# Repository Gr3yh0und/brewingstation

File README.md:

# Brewing Station

Firmware, hardware, and PCB design for a DIY automated beer brewing controller. An ESP32-based device reads mash temperature from multiple sensors, drives a [GGM IDS2 induction cooktop](https://www.ggmgastro.com/de-de-eur/induktionsherd-3-5-kw-1) through PID control, and integrates with [CraftBeerPi](https://web.craftbeerpi.com/) via MQTT.

This repo tracks the project's evolution across several hardware/firmware generations.

Credit: the GGM IDS2 induction cooktop's RS232/serial protocol — pulse timings, command frames, power levels, and error codes — was reverse-engineered by [InnuendoPi](https://github.com/InnuendoPi) in [MQTTDevice2](https://github.com/InnuendoPi/MQTTDevice2). Every generation in this repo builds on that work.

## Own projects (in order of development)

| Folder | Status | Board | Build system | Notes |
|---|---|---|---|---|
| [brewingstation](brewingstation/) | V1 | ESP32 (DOIT ESP32 DEVKIT V1) | Arduino IDE (`.ino`) or PlatformIO | One firmware, two hardware variants: [breadboard](brewingstation/hardware/breadboard/) and [fabricated PCB](brewingstation/hardware/pcb/). Documented in its own [README](brewingstation/README.md). |
| [brewingstation3](brewingstation3/) | **WIP** | ESP32-C6-WROOM-1U | PlatformIO | Full rewrite: PID mash control, multi-sensor support, safety shutdowns, brew timer, KiCad schematic, 3D-printable case. See [README](brewingstation3/README.md), [HARDWARE.md](brewingstation3/HARDWARE.md), [BOM.md](brewingstation3/BOM.md), [CASE.md](brewingstation3/CASE.md). |

`brewingstation` carries a `platformio.ini` (`src_dir = .`) alongside its `.ino`, so both PlatformIO and the Arduino IDE build from the same source file — pick whichever toolchain you prefer.

All generations share the same core idea: control the GGM IDS2 induction cooktop over its proprietary serial protocol, read temperature from DS18B20/PT100/PT1000/BME sensors, drive a couple of OLED displays and status LEDs, and talk to CraftBeerPi over MQTT.

`brewingstation3` is where active development happens; the earlier folders are kept as historical/reference hardware revisions. It is **work in progress**: firmware compiles but is not yet proven on real hardware — the PCB hasn't been soldered/assembled, nothing has been tested end-to-end, and the 3D-printable case hasn't been printed.

## Getting started

Each own-project folder is self-contained with its own README and config. In general:

1. Pick a generation — `brewingstation3` for new builds, the earlier folders for reference or repairing existing hardware.
2. Copy `config_example.h` (or `include/config_example.h` for `brewingstation3`) to `config.h` and fill in your MQTT/OTA settings (`brewingstation3` also provisions WiFi separately, via a WiFiManager captive portal on first boot — see its README). `config.h` is gitignored — never commit real credentials.
3. Build with PlatformIO (`pio run`) or open the `.ino` directly in the Arduino IDE — see that folder's README for board-specific notes.

The whole repo can also be opened as a single VS Code workspace via [brewingstation.code-workspace](brewingstation.code-workspace).

## Testing

`brewingstation3` has a native unit test suite for its hardware-independent logic (calibration math, button-ladder mapping, induction error codes) — runs on the host, no ESP32 toolchain or device required:

```sh
cd brewingstation3
pio test -e native
```

CI runs both the firmware build and this test suite on every push — see the badge above or [.github/workflows/build-brewingstation3.yml](.github/workflows/build-brewingstation3.yml).

## License

[MIT](LICENSE) — see [LICENSE](LICENSE) for the full text.

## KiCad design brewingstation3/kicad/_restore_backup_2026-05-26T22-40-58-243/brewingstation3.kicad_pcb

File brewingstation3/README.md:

# Brewing Station 3

Automated beer brewing temperature controller. Reads temperature from multiple sensors, controls a GGM IDS2 induction cooker via a proprietary serial protocol, and runs a PID loop to hold a target mash temperature. Integrates with CraftBeerPi 3 and 4 via MQTT.

**Status: work in progress.** Firmware compiles but is not yet proven on real hardware — the PCB hasn't been soldered/assembled, nothing has been tested end-to-end, and the 3D-printable case hasn't been printed.

**Board:** ESP32-C6-WROOM-1U (ESP32-C6-DevKitC-1-N8)  
**Toolchain:** PlatformIO + VS Code (see [platformio.ini](platformio.ini))  
**Schematic:** KiCad 10 — see [kicad/](kicad/)

| Document | Contents |
|---|---|
| [HARDWARE.md](HARDWARE.md) | Sensors, actuators, connectors, pin map, IDS2 protocol, displays |
| [BOM.md](BOM.md) | Full bill of materials with order links |
| [CASE.md](CASE.md) | 3D-printable enclosure — dimensions, assembly, panel layout |

## Releases

Versioned as `3.0.0-alpha.N` (SemVer, pre-1.0 track) while the hardware is unverified — every [release](../../releases) is marked **pre-release** on GitHub until the PCB is built, soldered, and confirmed working end-to-end, at which point it graduates to `3.0.0`. Tags use a plain `3.*` pattern (no `v` prefix) to avoid colliding with `brewingstation` (V1)'s `vX.Y.Z` tags.

Cutting a release: `git tag 3.0.0-alpha.N && git push origin 3.0.0-alpha.N` — this runs the native test suite as a gate, then builds and publishes binaries, a KiCad design snapshot, and the case source to a GitHub Release. See [.github/workflows/release-brewingstation3.yml](../.github/workflows/release-brewingstation3.yml).

---

## Software Features

### Brewing Control
- **PID temperature control** — Proportional on Measurement (P_ON_M) mode. Default tuning: P=45.27, I=0.2371, D=7.2. All parameters adjustable at runtime via MQTT. Setpoint can be configured while PID is off.
- **Induction cooker control** — GGM IDS2 controlled via a proprietary 33-bit pulse-width serial protocol. 6 discrete power levels (P0–P5); intermediate percentages achieved by PWM-cycling between adjacent levels in a 20-second window. Relay stays on for 60 seconds after power-off for fan cooldown.
- **Multi-sensor support** — Up to 5 sensors total: DS18B20 (OneWire, auto-detected), PT100X via MAX31865, BME680. Sensors auto-detected at boot; bad DS18B20 readings (-127°C) are discarded and the previous value retained.
- **Power cap** — Configurable maximum induction output percentage (`INDUCTION_POWER_CAP`, default 100%). Applied to both the PID output path and direct `heater/power` MQTT commands. Adjustable at runtime via `induction/cap` MQTT topic without reflashing.
- **Brew timer** — Countdown timer driven via MQTT (`timer/set`, `timer/control`). Supports start, pause, and reset. Remaining time shown on Display 1 when active. Expiry logged via syslog.
- **Safety shutdowns** — Three automatic cutoffs disable induction power and the PID: (1) sensor staleness: primary sensor has not reported for 30 seconds; (2) thermal runaway: temperature exceeds setpoint by more than 5°C; (3) cooker error codes: E3 overheat, E7 low voltage, or E8 high voltage received from the cooker RX line. All events are logged via syslog at CRIT severity.

### User Interface
- **Dual OLED display** — Display 1: runtime/clock/timer, PID target temperature, PID output %, Wi-Fi/MQTT status icons. Display 2: sensor temperatures, induction power level and percentage, fan indicator, PID active flag.
- **Button control** — 6 panel buttons on a single ADC pin (IO1) via resistor ladder. Each button directly sets the GGM IDS2 induction cooker to a fixed power level (0 / 20 / 40 / 60 / 80 / 100%). Debounced (250 ms). See button mapping table below.
- **Power-level LEDs** — 8 LEDs driven via PCF8574 I2C GPIO expander (address 0x20), active-LOW. The lit LED always reflects the current IDS2 power state: whichever power level is active, the corresponding LED turns on. The LED updates whenever the power level changes — whether set by a button press, MQTT command, or PID output. P6/P7 are spare outputs available for custom use.

### Network & Platform
- **CraftBeerPi 3 & 4** compatible via MQTT.
- **WiFi provisioning via captive portal** — WiFiManager opens an AP automatically on first boot or a failed connect, or can be forced by holding any panel button for ~2s at power-on. No WiFi credentials are stored in `config.h`. The same portal also lets you set the MQTT broker address, MQTT topic prefix, and OTA password without reflashing.
- **OTA firmware updates** — ArduinoOTA on port 8266, or via the web dashboard's upload form (`http://<ip>/update`); both password-protected (`OTA_PASSWORD` in `config.h`, changeable later via the WiFiManager portal).
- **Web dashboard** — three tabbed pages at `http://<ip>/`, with the hostname and running firmware version shown in the nav bar: **Status** (sensors, setpoint, PID/mode, induction power, relay/GPIO5, brew timer, WiFi signal, uptime, version — auto-refreshes every 5s, no login), **Update** (browser firmware upload, a link to the GitHub releases page, and a "Check for update" button that compares the running version against GitHub directly from the browser), and **Config** (current MQTT/WiFi/PID settings, with a JSON download for backup). Update and Config require the OTA password (HTTP Basic Auth).
- **mDNS** — Device advertises as `ESP-BREWING.local`.
- **Syslog** — UDP logging to backend server on port 514.
- **NTP time sync** — `configTzTime()` called after WiFi connects; POSIX timezone string configurable via `NTP_TIMEZONE` in `config.h`. When synced, Display 1 shows wall-clock time instead of uptime.
- **Hardware watchdog** — ESP32 task watchdog timer (`WDT_TIMEOUT_S`, default 30 s). Reboots the device if `loop()` stalls for any reason.

### Button Mapping

Each button sets the GGM IDS2 induction cooker to a fixed power level. The matching power-level LED lights up immediately after the button is pressed. See [HARDWARE.md](HARDWARE.md#button--led-panel-external--not-on-pcb) for wiring details.

| Button | Panel ref | ADC range | IDS2 power | LED |
|---|---|---|---|---|
| B1 | SW2 | 3200–3299 | 0% (off) | LD1 (LED_0) |
| B2 | SW3 | 3000–3199 | 20% | LD2 (LED_20) |
| B3 | SW4 | 2600–2999 | 40% | LD3 (LED_40) |
| B4 | SW5 | 2000–2599 | 60% | LD4 (LED_60) |
| B5 | SW6 | 1–1999 | 80% | LD5 (LED_80) |
| B6 | SW7 | 0 (ADC_BTN shorted to GND) | 100% | LD6 (LED_100) |

> The LEDs also update when the power level is changed via MQTT or PID output — the lit LED always reflects the **current** IDS2 state, not just the last button pressed.

---

## MQTT

All topics are built from `MQTT_ROOT_PATH / MQTT_DEVICE` — set in `config.h` as first-boot defaults, changeable afterward via the WiFiManager portal (persisted to `/netconfig.json`).

| Topic | Direction | Payload fields |
|---|---|---|
| `.../sensor/N` | publish | `temp` (°C), `ts` |
| `.../induction` | publish | `relay`, `active`, `power`, `level`, `error`, `cap`, `ts` |
| `.../induction/set` | subscribe | `power` (0–100); `state "off"` cuts power |
| `.../induction/cap` | subscribe | `cap` (0–100) — runtime power ceiling |
| `.../pid` | publish | `enabled`, `mode`, `setpoint`, `input`, `output`, `diff`, `P`, `I`, `D`, `ts` |
| `.../pid/enable` | subscribe | `enabled` (bool) |
| `.../pid/reset` | subscribe | _(any payload)_ — resets PID output to 0 |
| `.../pid/p` | subscribe | `P` (float) |
| `.../pid/i` | subscribe | `I` (float) |
| `.../pid/d` | subscribe | `D` (float) |
| `.../pid/setpoint` | subscribe | `setpoint` (float, 0–100°C) |
| `.../timer` | publish | `running`, `paused`, `remaining` (s), `duration` (s), `ts` |
| `.../timer/set` | subscribe | `duration` (seconds) |
| `.../timer/ctl` | subscribe | `cmd`: `"start"` / `"pause"` / `"reset"` |
| `.../device` | publish | `uptime`, `heap`, `rssi`, `version`, `mode`, `ts` |
| `.../device/mode` | subscribe | `mode`: `"standalone"` / `"slave"` |
| `.../relay` | publish | `state`, `remaining`, `ts` |
| `.../relay/set` | subscribe | `state`: `"on"` / `"off"`; optional `duration` (s) |
| `.../gpio_ext` | publish | `state`, `remaining`, `ts` |
| `.../gpio_ext/set` | subscribe | `state`: `"on"` / `"off"`; optional `duration` (s) |

---

## Configuration

Copy `include/config_example.h` to `include/config.h` and fill in your values. `config.h` is gitignored.

```cpp
#define HOSTNAME        "ESP-BREWING"
#define SERVER_ADDRESS  "192.168.0.x"   // Raspberry Pi IP
#define MQTT_ROOT_PATH  "home"
#define MQTT_DEVICE     "brewery"
```

**WiFi credentials are not set in `config.h`.** On first boot (or whenever no saved WiFi credentials connect), the device opens a WiFiManager captive-portal AP — connect to it from a phone/laptop and submit your WiFi SSID/password, MQTT broker address, MQTT topic prefix, and OTA password through its web form. These are stored in the ESP32's NVS (WiFi) and `/netconfig.json` (the rest), surviving reboots and reflashes. To reprovision later without clearing flash, hold any panel button for ~2s at power-on to force the portal open again.

**PT100X vs PT1000:** Default is PT1000 (`R_NOM=1000`, `R_REF=4300`). Change both to `100` / `430` for PT100.

**PID tuning:** Default values (`P=45.27`, `I=0.2371`, `D=7.2`) are tuned for a specific vessel. Adjust `PID_DEFAULT_P/I/D` in `config.h`. Values can also be changed at runtime via MQTT.

**Button ADC thresholds:** `BUTTON_THRESHOLD_B1–B5` depend on actual resistor values. Measure with serial monitor and adjust if buttons trigger at the wrong levels.

**Safety thresholds:** `PID_SAFETY_OVERSHOOT` (default 5°C) and `SENSOR_STALE_TIMEOUT_MS` (default 30s).

**Power cap:** `INDUCTION_POWER_CAP` (default 100%). Override at runtime via `induction/cap` MQTT.

**Watchdog:** `WDT_TIMEOUT_S` (default 30 s).

**NTP:** `NTP_SERVER` (default `pool.ntp.org`) and `NTP_TIMEZONE` (POSIX string). See [nayarsystems/posix_tz_db](https://github.com/nayarsystems/posix_tz_db).

---

## Build & Flash (PlatformIO)

```sh
# Build
pio run -e esp32c6

# Upload via USB-CDC (no external USB-UART chip needed)
pio run -e esp32c6 -t upload

# Serial monitor
pio device monitor

# Debug build (verbose ESP-IDF logs)
pio run -e esp32c6_debug
```

Or use the PlatformIO sidebar in VS Code (Build ✓ / Upload → / Monitor icons).

---

## Libraries

All dependencies are managed by PlatformIO via `platformio.ini`.

| Library | Author | Constraint | Installed |
|---|---|---|---|
| PubSubClient | Nick O'Leary | `^2.8` | 2.8 |
| ArduinoJson | Benoit Blanchon | `^7.0` | 7.4.3 |
| Syslog | Martin Sloup (arcao) | `^2.0` | 2.0.0 |
| Arduino-PID-Library | Brett Beauregard | `^1.2` | 1.2.1 |
| OneWire | Paul Stoffregen | local `lib/` | 2.3.8 (patched) |
| DallasTemperature | Miles Burton | `^3.9` | 3.11.0 |
| Adafruit Unified Sensor | Adafruit | `^1.1` | 1.1.15 |
| Adafruit MAX31865 | Adafruit | `^1.1` | 1.6.2 |
| Adafruit BME680 | Adafruit | `^2.2` | 2.3.0 |
| Adafruit GFX | Adafruit | `^1.11` | 1.12.6 |
| Adafruit SSD1306 | Adafruit | `^2.5` | 2.5.16 |
| PCF8574 | Rob Tillaart | `^0.3` | 0.3.9 |
| arduino-timer | contrem | unpinned | 3.0.1 |

**OneWire note:** Kept as a local copy in `lib/OneWire/` because the upstream release does not handle the ESP32-C6 GPIO register struct (typed fields requiring `.val` in arduino-esp32 3.x). The patch adds `|| CONFIG_IDF_TARGET_ESP32C6` to each `#if CONFIG_IDF_TARGET_ESP32C3` guard in `util/OneWire_direct_gpio.h`.

**Platform:** pioarduino community fork (`pioarduino/platform-espressif32 @ stable`). The official `espressif32` platform references a RISC-V toolchain package (`toolchain-riscv32-esp @ 13.2.0+20240530`) that was removed from the PlatformIO registry; the pioarduino fork bundles the toolchain directly. Bundles arduino-esp32 3.x, which is required for ESP32-C6 support.

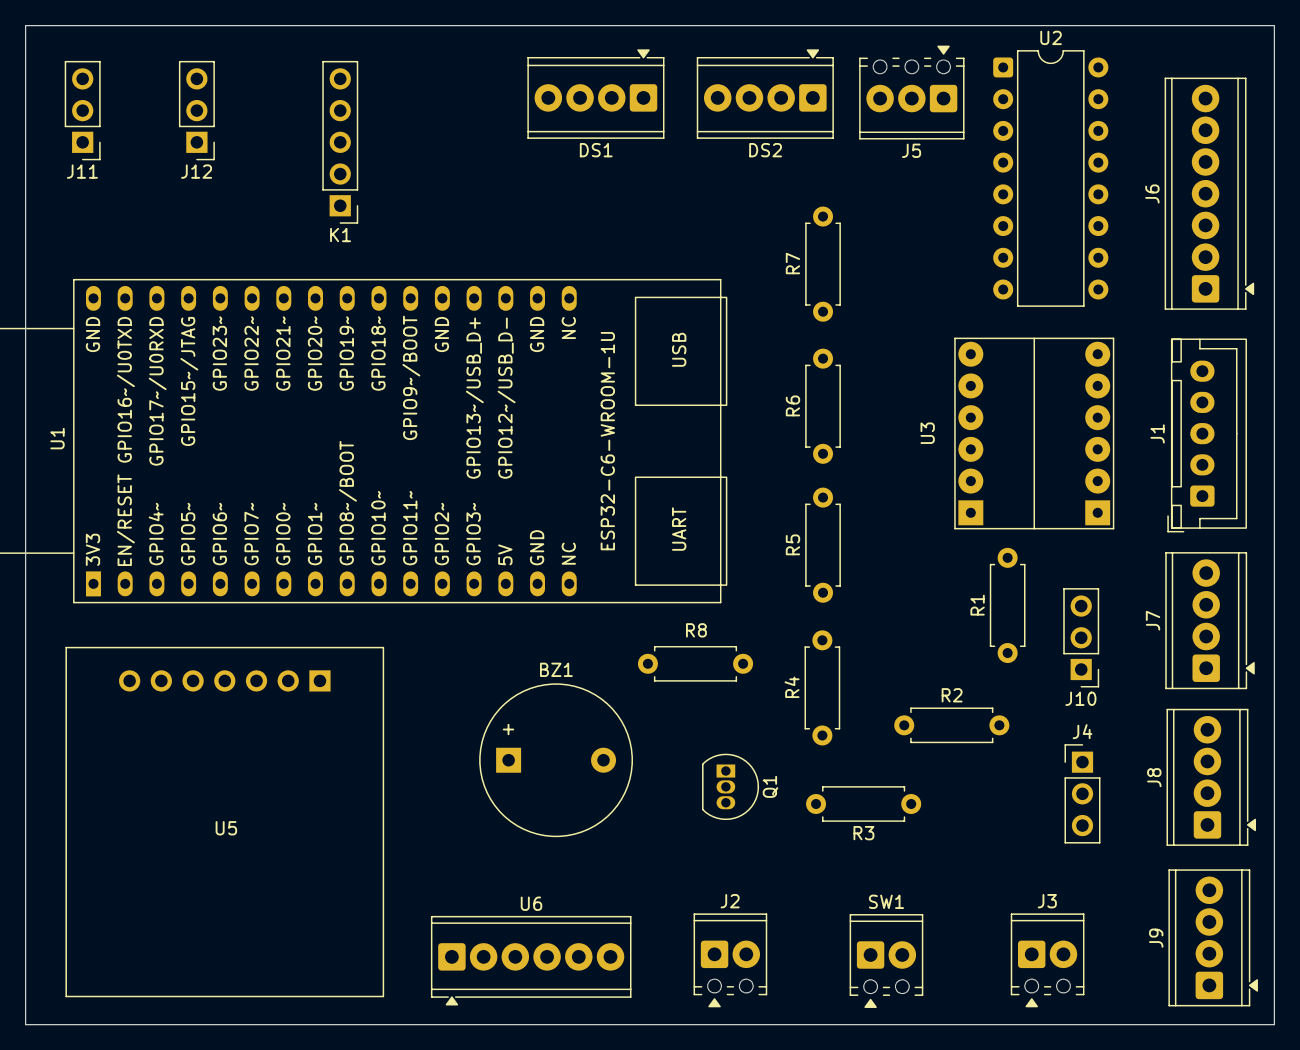
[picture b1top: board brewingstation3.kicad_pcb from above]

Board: 2 copper layers, 100.0 x 80.0 mm, 31 parts (0 on the bottom side), 43 nets, no tracks yet.

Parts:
BZ1: CPM121; Buzzer_12x9.5RM7.6
DS1: SSD1306_0x3C; TerminalBlock_Phoenix_MPT-0,5-4-2.54_1x04_P2.54mm_Horizontal
DS2: SSD1306_0x3D; TerminalBlock_Phoenix_MPT-0,5-4-2.54_1x04_P2.54mm_Horizontal
J1: GGM_IDS2; JST_XH_B5B-XH-A_1x05_P2.50mm_Vertical
J2: GPIO_EXT_Conn; TerminalBlock_Phoenix_MPT-0,5-2-2.54_1x02_P2.54mm_Horizontal
J3: PExt_Connector; TerminalBlock_Phoenix_MPT-0,5-2-2.54_1x02_P2.54mm_Horizontal
J4: PJump; PinHeader_1x03_P2.54mm_Vertical
J5: BTN_Panel; TerminalBlock_Phoenix_MPT-0,5-3-2.54_1x03_P2.54mm_Horizontal
J6: LED_Panel; TerminalBlock_Phoenix_MPT-0,5-7-2.54_1x07_P2.54mm_Horizontal
J7: DS18B20_1; TerminalBlock_Phoenix_MPT-0,5-4-2.54_1x04_P2.54mm_Horizontal
J8: DS18B20_2; TerminalBlock_Phoenix_MPT-0,5-4-2.54_1x04_P2.54mm_Horizontal
J9: DS18B20_3; TerminalBlock_Phoenix_MPT-0,5-4-2.54_1x04_P2.54mm_Horizontal
J10: PWR_TAP; PinHeader_1x03_P2.54mm_Vertical
J11: UART_HDR; PinHeader_1x03_P2.54mm_Vertical
J12: GPIO_FREE; PinHeader_1x03_P2.54mm_Vertical
K1: Relay_5V_3V3trig; PinHeader_1x05_P2.54mm_Vertical
Q1: BC547B; TO-92_Inline
R1: 4k7; R_Axial_DIN0207_L6.3mm_D2.5mm_P7.62mm_Horizontal
R2, R3, R4, R5, R6, R7: 330R; R_Axial_DIN0207_L6.3mm_D2.5mm_P7.62mm_Horizontal
R8: 1k; R_Axial_DIN0207_L6.3mm_D2.5mm_P7.62mm_Horizontal
SW1: PSw_Connector; TerminalBlock_Phoenix_MPT-0,5-2-2.54_1x02_P2.54mm_Horizontal
U1: ESP32-C6-WROOM-1U; ESP32-C6-DevKitC-1
U2: PCF8574; DIP-16_W7.62mm
U3: LevelShifter_4CH
U5: MAX31865; MAX31865_Module
U6: BME680; TerminalBlock_Phoenix_MPT-0,5-6-2.54_1x06_P2.54mm_Horizontal

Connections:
+3V3: DS1.2 (VCC), DS2.2 (VCC), J5.1 (+3V3), J7.2 (+3V3), J8.2 (+3V3), J9.2 (+3V3), J10.2 (+3V3), R1.1, U1.1 (+3V3), U1.2 (EN), U2.2 (VDD), U3.3 (LV), U5.1 (VCC), U6.1 (VCC)
+5V: BZ1.1 (+), J10.3 (+5V), K1.1 (VCC), SW1.2 (B), U1.14 (+5V), U3.9 (HV)
/ADC_BTN: J5.2 (ADC_BTN), U1.8 (IO1)
/BUZZER_CTRL: R8.1, U1.27 (IO22)
/BZ_B: Q1.1 (B), R8.2
/BZ_N: BZ1.2 (-), Q1.2 (C)
/CS_BME: U1.12 (IO2), U6.6 (CSB)
/CS_MAX: U1.6 (IO7), U5.6 (CS)
/GPIO_EXT: J2.1 (SIG), U3.12 (HV4)
/GPIO_EXT_LV: U1.13 (IO3), U3.6 (LV4)
/I2C_SCL: DS1.3 (SCL), DS2.3 (SCL), U1.11 (IO11), U2.7 (SCL)
/I2C_SDA: DS1.4 (SDA), DS2.4 (SDA), U1.10 (IO10), U2.8 (SDA)
/IDS2_5V: J1.1 (VCC), J4.1 (IDS2)
/IDS2_BLUE: J1.5 (BLUE), U3.11 (HV3)
/IDS2_BLU_LV: U1.25 (IO20), U3.5 (LV3)
/IDS2_WHITE: J1.3 (WHITE), U3.7 (HV1)
/IDS2_WHT_LV: U1.23 (IO18), U3.1 (LV1)
/IDS2_YELLOW: J1.4 (YELLOW), U3.8 (HV2)
/IDS2_YEL_LV: U1.24 (IO19), U3.2 (LV2)
/IO15: J12.2 (IO15), U1.29 (IO15)
/IO23: J12.3 (IO23), U1.28 (IO23)
/LED_0: J6.2 (LED_0), U2.10 (P1)
/LED_20: J6.3 (LED_20), U2.11 (P2)
/LED_40: J6.4 (LED_40), U2.12 (P3)
/LED_60: J6.5 (LED_60), U2.13 (P4)
/LED_80: J6.6 (LED_80), U2.14 (P5)
/LED_100: J6.7 (LED_100), R7.2
/OneWire: J7.3 (DQ), J8.3 (DQ), J9.3 (DQ), R1.2, U1.26 (IO21)
/PCF_P0: R2.1, U2.9 (P0)
/PEXT_5V: J3.1 (VCC), J4.3 (PEXT)
/PJUMP_OUT: J4.2 (5V), SW1.1 (A)
/RELAY_CTRL: K1.3 (IN), U1.7 (IO0)
/SPI_CLK: U1.5 (IO6), U5.5 (SCK), U6.3 (SCK)
/SPI_MISO: U1.4 (IO5), U5.4 (SDO), U6.5 (SDO)
/SPI_MOSI: U1.3 (IO4), U5.3 (SDI), U6.4 (SDI)
/UART_RX: J11.3 (RX_IO17), U1.30 (IO17~RX)
/UART_TX: J11.2 (TX_IO16), U1.31 (IO16~TX)
GND: DS1.1 (GND), DS2.1 (GND), J1.2 (GND), J2.2 (GND), J3.2 (GND), J5.3 (GND), J6.1 (GND), J7.1 (GND), J8.1 (GND), J9.1 (GND), J10.1 (GND), J11.1 (GND), J12.1 (GND), K1.2 (GND), Q1.3 (E), U1.15 (GND), U1.18 (GND), U1.21 (GND), U1.32 (GND), U2.1 (VSS), U2.3 (A0), U2.4 (A1), U2.5 (A2), U3.4 (GND), U3.10 (GND), U5.2 (GND), U6.2 (GND)
unnamed: R2.2, R3.1
unnamed: R3.2, R4.1
unnamed: R4.2, R5.1
unnamed: R5.2, R6.1
unnamed: R6.2, R7.1

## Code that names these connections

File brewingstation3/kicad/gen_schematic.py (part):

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
# Pin numbers match PCM_Espressif:ESP32-C6-DevKitC-1 footprint pads 1-32.
# Left rail: pad 1 (top) → pad 16 (bottom). Right rail: pad 32 (top) → pad 17 (bottom).
# NOTE: GPIO14 is NOT exposed on DevKitC-1 — GPIO_EXT reassigned to IO3 (pad 13).
ESP32_LEFT = [
    ("+3V3",    "1",  PWR_OUT),  # 3.3V output from DevKit LDO
    ("EN",      "2",  INP),
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    ("IO10",    "10", BI),
    ("IO11",    "11", BI),
    ("IO2",     "12", BI),
    ("IO3",     "13", BI),       # GPIO_EXT (IO14 not on DevKitC-1, update firmware)
    ("+5V",     "14", PWR_IN),   # DevKit VIN — powered from +5V rail
    ("GND",     "15", PWR_IN),
    ("NC",      "16", PASS),
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    sym_def("Brew:GGM_IDS2",        "J","GGM_IDS2",            IDS2_LEFT, IDS2_RIGHT, body_w=10),
    sym_def("Brew:Relay_Module",    "K","Relay_5V",             RELAY_LEFT, RELAY_RIGHT, body_w=10),
    sym_def("Brew:R",               "R","R",                   R_LEFT, R_RIGHT, body_w=5),
    sym_def("Brew:Conn_GPIO_EXT",   "J","GPIO_EXT",            GPIOEXT_LEFT, GPIOEXT_RIGHT, body_w=10),
    sym_def("Brew:Conn_PExt",      "J","PExt_5V",             PEXT_LEFT,   PEXT_RIGHT,   body_w=10),
    sym_def("Brew:PJump",          "J","PJump",               PJUMP_LEFT,  PJUMP_RIGHT,  body_w=10),
    sym_def("Brew:Conn_PSw",       "J","PSw_Conn",            PSW_LEFT,    PSW_RIGHT,    body_w=10),
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    "IO22": "NC",
    "IO23": "NC",
    # Power nets
    "IDS2_5V":   "5V tap from IDS2 connector VCC pin",
    "PEXT_5V":   "5V from external USB charger connector",
    "PJUMP_OUT": "PJump center pin → PSw → +5V rail",
}

instances = []
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
# Left-side signal assignments (ordered to match ESP32_LEFT / pads 1-16)
LEFT_SIGNALS = ["+3V3","EN","IO4","IO5","IO6","IO7","IO0","IO1","IO8","IO10","IO11","IO2","IO3","+5V","GND","NC"]
LEFT_NETS =    [None,  None,"SPI_MOSI","SPI_MISO","SPI_CLK","CS_MAX","ONE_WIRE","ADC_BTN",None,"I2C_SDA","I2C_SCL","CS_BME","GPIO_EXT_LV",None,None,None]

for i, (sig, net) in enumerate(zip(LEFT_SIGNALS, LEFT_NETS)):
    px, py = LP[i]
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# ~INT (left pin 5) — no connect
nc_out.append(no_connect(LP2[5][0], LP2[5][1]))
# SCL, SDA net labels (left pins 6,7)
labels_out.append(net_label("I2C_SCL", LP2[6][0]-1.27, LP2[6][1], 180))
wires_out.append(wire(LP2[6][0]-1.27, LP2[6][1], LP2[6][0], LP2[6][1]))
labels_out.append(net_label("I2C_SDA", LP2[7][0]-1.27, LP2[7][1], 180))
wires_out.append(wire(LP2[7][0]-1.27, LP2[7][1], LP2[7][0], LP2[7][1]))

# P0-P5 → intermediate PCF_PX nets (resistors sit between PCF and J6 LED_XPCT nets)
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RP3 = [rpin(U3x,U3y,i,n3r) for i in range(n3r)]

# LV side (left): LV1(0) LV2(1) LV-supply(2) GND(3) LV3(4) LV4(5)
# Channels 1-4 map: LV1=IDS2_WHITE_LV, LV2=IDS2_YEL_LV, LV3=IDS2_BLU_LV, LV4=GPIO_EXT_LV
labels_out.append(net_label("IDS2_WHITE_LV", LP3[0][0]-1.27, LP3[0][1], 180))
wires_out.append(wire(LP3[0][0]-1.27, LP3[0][1], LP3[0][0], LP3[0][1]))
labels_out.append(net_label("IDS2_YEL_LV",  LP3[1][0]-1.27, LP3[1][1], 180))
wires_out.append(wire(LP3[1][0]-1.27, LP3[1][1], LP3[1][0], LP3[1][1]))
pwr_out.append(place_pwr("+3V3", LP3[2][0]-P, LP3[2][1]))   # LV supply
wires_out.append(wire(LP3[2][0]-P, LP3[2][1], LP3[2][0], LP3[2][1]))
pwr_out.append(place_pwr("GND",  LP3[3][0]-P, LP3[3][1]))
wires_out.append(wire(LP3[3][0]-P, LP3[3][1], LP3[3][0], LP3[3][1]))
labels_out.append(net_label("IDS2_BLU_LV",  LP3[4][0]-1.27, LP3[4][1], 180))
wires_out.append(wire(LP3[4][0]-1.27, LP3[4][1], LP3[4][0], LP3[4][1]))
labels_out.append(net_label("GPIO_EXT_LV",  LP3[5][0]-1.27, LP3[5][1], 180))
wires_out.append(wire(LP3[5][0]-1.27, LP3[5][1], LP3[5][0], LP3[5][1]))

# HV side (right): HV1(0) HV2(1) HV-supply(2) GND(3) HV3(4) HV4(5)
labels_out.append(net_label("IDS2_WHITE",  RP3[0][0]+1.27, RP3[0][1]))
wires_out.append(wire(RP3[0][0], RP3[0][1], RP3[0][0]+1.27, RP3[0][1]))
labels_out.append(net_label("IDS2_YELLOW", RP3[1][0]+1.27, RP3[1][1]))
wires_out.append(wire(RP3[1][0], RP3[1][1], RP3[1][0]+1.27, RP3[1][1]))
pwr_out.append(place_pwr("+5V", RP3[2][0]+P, RP3[2][1]))    # HV supply
wires_out.append(wire(RP3[2][0]+P, RP3[2][1], RP3[2][0], RP3[2][1]))
pwr_out.append(place_pwr("GND", RP3[3][0]+P, RP3[3][1]))
wires_out.append(wire(RP3[3][0]+P, RP3[3][1], RP3[3][0], RP3[3][1]))
labels_out.append(net_label("IDS2_BLUE",   RP3[4][0]+1.27, RP3[4][1]))
wires_out.append(wire(RP3[4][0], RP3[4][1], RP3[4][0]+1.27, RP3[4][1]))
labels_out.append(net_label("GPIO_EXT",    RP3[5][0]+1.27, RP3[5][1]))
wires_out.append(wire(RP3[5][0], RP3[5][1], RP3[5][0]+1.27, RP3[5][1]))


# ── J7,J8,J9  DS18B20 sensors — GX12 4-pin panel-mount connectors  ──────────
# Sensors are external, wired via GX12 4-pin aviation connectors.
# GX12 pin map: 1=GND, 2=+3V3, 3=DQ (OneWire), 4=NC
for _ds_idx, (_DSx, _DSy, _DSref) in enumerate([
        (305.0, 35.0, "J7"),
        (305.0, 65.0, "J8"),
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    wires_out.append(wire(LP_d[0][0]-P, LP_d[0][1], LP_d[0][0], LP_d[0][1]))
    pwr_out.append(place_pwr("+3V3", LP_d[1][0]-P, LP_d[1][1]))
    wires_out.append(wire(LP_d[1][0]-P, LP_d[1][1], LP_d[1][0], LP_d[1][1]))
    labels_out.append(net_label("I2C_SCL", LP_d[2][0]-1.27, LP_d[2][1], 180))
    wires_out.append(wire(LP_d[2][0]-1.27, LP_d[2][1], LP_d[2][0], LP_d[2][1]))
    labels_out.append(net_label("I2C_SDA", LP_d[3][0]-1.27, LP_d[3][1], 180))
    wires_out.append(wire(LP_d[3][0]-1.27, LP_d[3][1], LP_d[3][0], LP_d[3][1]))


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                       pins=IDS2_LEFT+IDS2_RIGHT))
LP_j = [lpin(J1x,J1y,i,len(IDS2_LEFT),10) for i in range(len(IDS2_LEFT))]
# VCC tap → IDS2_5V net (feeds PJump)
labels_out.append(net_label("IDS2_5V", LP_j[0][0]-1.27, LP_j[0][1], 180))
wires_out.append(wire(LP_j[0][0]-1.27, LP_j[0][1], LP_j[0][0], LP_j[0][1]))
# GND
pwr_out.append(place_pwr("GND", LP_j[1][0]-P, LP_j[1][1]))
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wires_out.append(wire(LP_k[0][0]-P, LP_k[0][1], LP_k[0][0], LP_k[0][1]))
pwr_out.append(place_pwr("GND", LP_k[1][0]-P, LP_k[1][1]))
wires_out.append(wire(LP_k[1][0]-P, LP_k[1][1], LP_k[1][0], LP_k[1][1]))
labels_out.append(net_label("RELAY_CTRL", LP_k[2][0]-1.27, LP_k[2][1], 180))
wires_out.append(wire(LP_k[2][0]-1.27, LP_k[2][1], LP_k[2][0], LP_k[2][1]))
# NO and COM are output terminals — no connect for now (user wires load)
nc_out.append(no_connect(LP_k[3][0], LP_k[3][1]))
nc_out.append(no_connect(LP_k[4][0], LP_k[4][1]))


# ── J2  GPIO_EXT  ─────────────────────────────────────────────────────────────
J2x, J2y = 305.0, 310.0
instances.append(place("Brew:Conn_GPIO_EXT","J2","GPIO_EXT_Conn", J2x, J2y,
                       fp="Connector_PinHeader_2.54mm:PinHeader_1x02_P2.54mm_Vertical",
                       pins=GPIOEXT_LEFT+GPIOEXT_RIGHT))
LP_j2 = [lpin(J2x,J2y,i,len(GPIOEXT_LEFT),10) for i in range(len(GPIOEXT_LEFT))]
labels_out.append(net_label("GPIO_EXT", LP_j2[0][0]-1.27, LP_j2[0][1], 180))
wires_out.append(wire(LP_j2[0][0]-1.27, LP_j2[0][1], LP_j2[0][0], LP_j2[0][1]))
pwr_out.append(place_pwr("GND", LP_j2[1][0]-P, LP_j2[1][1]))
wires_out.append(wire(LP_j2[1][0]-P, LP_j2[1][1], LP_j2[1][0], LP_j2[1][1]))
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                       pins=PEXT_LEFT+PEXT_RIGHT))
LP_j3 = [lpin(J3x,J3y,i,len(PEXT_LEFT),10) for i in range(len(PEXT_LEFT))]
# VCC → PEXT_5V net (feeds PJump)
labels_out.append(net_label("PEXT_5V", LP_j3[0][0]-1.27, LP_j3[0][1], 180))
wires_out.append(wire(LP_j3[0][0]-1.27, LP_j3[0][1], LP_j3[0][0], LP_j3[0][1]))
# GND
pwr_out.append(place_pwr("GND", LP_j3[1][0]-P, LP_j3[1][1]))
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                       fp="Connector_PinHeader_2.54mm:PinHeader_1x03_P2.54mm_Vertical",
                       pins=PJUMP_LEFT+PJUMP_RIGHT))
LP_j4 = [lpin(J4x,J4y,i,len(PJUMP_LEFT),10) for i in range(len(PJUMP_LEFT))]
labels_out.append(net_label("IDS2_5V",   LP_j4[0][0]-1.27, LP_j4[0][1], 180))
wires_out.append(wire(LP_j4[0][0]-1.27, LP_j4[0][1], LP_j4[0][0], LP_j4[0][1]))
labels_out.append(net_label("PJUMP_OUT", LP_j4[1][0]-1.27, LP_j4[1][1], 180))
wires_out.append(wire(LP_j4[1][0]-1.27, LP_j4[1][1], LP_j4[1][0], LP_j4[1][1]))
labels_out.append(net_label("PEXT_5V",   LP_j4[2][0]-1.27, LP_j4[2][1], 180))
wires_out.append(wire(LP_j4[2][0]-1.27, LP_j4[2][1], LP_j4[2][0], LP_j4[2][1]))


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                       pins=PSW_LEFT+PSW_RIGHT))
LP_sw7 = [lpin(SW7x,SW7y,i,len(PSW_LEFT),10) for i in range(len(PSW_LEFT))]
# A side: from PJump output
labels_out.append(net_label("PJUMP_OUT", LP_sw7[0][0]-1.27, LP_sw7[0][1], 180))
wires_out.append(wire(LP_sw7[0][0]-1.27, LP_sw7[0][1], LP_sw7[0][0], LP_sw7[0][1]))
# B side: to +5V rail
pwr_out.append(place_pwr("+5V", LP_sw7[1][0]-P, LP_sw7[1][1]))
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LP_j5 = [lpin(J5x,J5y,i,len(JBTN_LEFT),10) for i in range(len(JBTN_LEFT))]
pwr_out.append(place_pwr("+3V3", LP_j5[0][0]-P, LP_j5[0][1]))
wires_out.append(wire(LP_j5[0][0]-P, LP_j5[0][1], LP_j5[0][0], LP_j5[0][1]))
labels_out.append(net_label("ADC_BTN", LP_j5[1][0]-1.27, LP_j5[1][1], 180))
wires_out.append(wire(LP_j5[1][0]-1.27, LP_j5[1][1], LP_j5[1][0], LP_j5[1][1]))
pwr_out.append(place_pwr("GND", LP_j5[2][0]-P, LP_j5[2][1]))
wires_out.append(wire(LP_j5[2][0]-P, LP_j5[2][1], LP_j5[2][0], LP_j5[2][1]))
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    (date "2026-05-24")
    (rev "1.0")
    (comment 1 "ESP32-C6-WROOM-1U · PCF8574 LED expander · TXS0104E level shifter · DS18B20 ×3")
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
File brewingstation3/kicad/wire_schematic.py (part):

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NL = len(ESP32_L)
# Left pin wiring
LEFT_NETS = [None, None, "CS_MAX","SPI_CLK","SPI_MISO","SPI_MOSI",
             "BUZZER_CTRL","ADC_BTN", None,"GPIO10","OneWire","CS_BME","GPIO3_ADC",
             None, None, None]
LEFT_PWR  = ["+3V3", "+3V3", None,None,None,None, None,None, None,None,None,None,None,
             "+5V","GND", None]
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
NR = len(ESP32_R)
# Right pin wiring
RIGHT_NETS = [None, "UART_TX","UART_RX","GPIO15","I2C_SDA","I2C_SCL",
              "RELAY_CTRL","IDS2_BLU_LV","IDS2_YEL_LV","IDS2_WHT_LV",
              None, None, None, None, None, None]
RIGHT_PWR  = ["GND", None,None,None,None,None, None,None,None,None,
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R1x = cx(55.88); R1y = cy(121.92, 1)
lx1,ly1 = lpin(R1x,R1y,0,1,bw=5)
rx1,ry1 = rpin(R1x,R1y,0,1,bw=5)
wires.append(wseg(rx1, ry1, OW_BUS_X, ry1))  # right pin → OneWire bus
pwr_l("+3V3",    lx1, ly1)

# ── OneWire bus (split at each T-junction + explicit junctions) ───────────────
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U5x = cx(82.55); U5y = cy(30.48, 7)
pwr_l("+3V3",    *lpin(U5x,U5y,0,7), stub=2*P)
pwr_l("GND",     *lpin(U5x,U5y,1,7), stub=P)
lbl_l("SPI_MOSI",*lpin(U5x,U5y,2,7))
lbl_l("SPI_MISO",*lpin(U5x,U5y,3,7))
lbl_l("SPI_CLK", *lpin(U5x,U5y,4,7))
lbl_l("CS_MAX",  *lpin(U5x,U5y,5,7))
nc(*lpin(U5x,U5y,6,7))   # DRDY unused

# ── U6  BME680 ────────────────────────────────────────────────────────────────
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U6x = cx(82.55); U6y = cy(63.50, 6)
pwr_l("+3V3",    *lpin(U6x,U6y,0,6), stub=2*P)
pwr_l("GND",     *lpin(U6x,U6y,1,6), stub=P)
lbl_l("SPI_CLK", *lpin(U6x,U6y,2,6))
lbl_l("SPI_MOSI",*lpin(U6x,U6y,3,6))
lbl_l("SPI_MISO",*lpin(U6x,U6y,4,6))
lbl_l("CS_BME",  *lpin(U6x,U6y,5,6))

# ── DS1/DS2  OLEDs ────────────────────────────────────────────────────────────
for ref, ya in [("DS1",80.01),("DS2",102.87)]:
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    dx = cx(232.41); dy = cy(ya, 4)
    pwr_l("GND",     *lpin(dx,dy,0,4), stub=P)
    pwr_l("+3V3",    *lpin(dx,dy,1,4), stub=2*P)
    lbl_l("I2C_SCL", *lpin(dx,dy,2,4))
    lbl_l("I2C_SDA", *lpin(dx,dy,3,4))

# ── U3  BSS138 level shifter ──────────────────────────────────────────────────
comps.append(place("Brew:LevelShifter_4CH","U3","LevelShifter_4CH", 142.24, 170.18,
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                   pins_l=LS_L, pins_r=LS_R))
U3x = cx(142.24); U3y = cy(170.18, max(len(LS_L),len(LS_R)))
nc(*lpin(U3x,U3y,0,6))                        # ch1 LV — nc
lbl_l("IDS2_WHT_LV", *lpin(U3x,U3y,1,6))    # ch2: WHITE — aligns with J1 pin3
pwr_l("+3V3",         *lpin(U3x,U3y,2,6), stub=2*P)
pwr_l("GND",          *lpin(U3x,U3y,3,6), stub=P)
lbl_l("IDS2_YEL_LV", *lpin(U3x,U3y,4,6))    # ch3: YELLOW — aligns with J1 pin4
lbl_l("IDS2_BLU_LV", *lpin(U3x,U3y,5,6))    # ch4: BLUE — aligns with J1 pin5
nc(*rpin(U3x,U3y,0,6))                        # ch1 HV — nc
lbl_r("IDS2_WHT_HV", *rpin(U3x,U3y,1,6))    # ch2 HV: WHITE
pwr_r("+5V",          *rpin(U3x,U3y,2,6), stub=2*P)
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                   fp=phoenix(5),
                   pins_l=IDS2_L))
J1x = cx(212.09); J1y = cy(171.45, 5)
lbl_l("IDS2_5V",     *lpin(J1x,J1y,0,5))
pwr_l("GND",          *lpin(J1x,J1y,1,5))
lbl_l("IDS2_WHT_HV", *lpin(J1x,J1y,2,5))
lbl_l("IDS2_YEL_HV", *lpin(J1x,J1y,3,5))
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K1x = cx(232.41); K1y = cy(59.69, 3)
pwr_l("+5V",          *lpin(K1x,K1y,0,3), stub=2*P)
pwr_l("GND",          *lpin(K1x,K1y,1,3), stub=P)
lbl_l("RELAY_CTRL",   *lpin(K1x,K1y,2,3))


# ── J3  PExt external 5V input ────────────────────────────────────────────────
comps.append(place("Brew:Conn_PExt","J3","PExt_Conn", 125.73, 27.94,
                   fp=phoenix(2), pins_l=PEXT_L))
J3x = cx(125.73); J3y = cy(27.94, 2)
lbl_l("PEXT_5V", *lpin(J3x,J3y,0,2))
pwr_l("GND",      *lpin(J3x,J3y,1,2))

# ── J4  PSource power source selector ────────────────────────────────────────
# Pin 1 (top) = IDS2_5V, Pin 2 (middle) = PSOURCE_OUT, Pin 3 (bottom) = PEXT_5V
# A jumper cap bridges one source to the common output.
comps.append(place("Brew:PSource","J4","PSource", 175.26, 33.02,
                   fp="Connector_PinHeader_2.54mm:PinHeader_1x03_P2.54mm_Vertical",
                   pins_l=PJMP_L))
J4x = cx(175.26); J4y = cy(33.02, 3)
lbl_l("IDS2_5V",   *lpin(J4x,J4y,0,3))
lbl_l("PSOURCE_OUT", *lpin(J4x,J4y,1,3))
lbl_l("PEXT_5V",   *lpin(J4x,J4y,2,3))

# ── SW1  Power switch (PSource output → +5V rail) ────────────────────────────
comps.append(place("Brew:Conn_PSw","SW1","PSw_Conn", 138.43, 46.99,
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pwr_l("GND",      *lpin(U2x,U2y,3,8), stub=2*P)   # A1
pwr_l("GND",      *lpin(U2x,U2y,4,8), stub=P)     # A2
nc(*lpin(U2x,U2y,5,8))                   # ~INT
lbl_l("I2C_SCL",  *lpin(U2x,U2y,6,8))
lbl_l("I2C_SDA",  *lpin(U2x,U2y,7,8))
LED_PCTS = [0,20,40,60,80,100]
# Direct wires from U2 P0-P7 to LED resistors R2-R7,R15,R16
# Staggered corner_x: min(i,7-i)*P from rpin_x; i=0/7 go straight (no horiz stub)
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                   pins_l=UART_HDR_L))
J11x = cx(232.41); J11y = cy(39.37, 3)
pwr_l("GND",      *lpin(J11x,J11y,0,3))
lbl_l("UART_TX",  *lpin(J11x,J11y,1,3))
lbl_l("UART_RX",  *lpin(J11x,J11y,2,3))

# ── J12  GPIO free header ─────────────────────────────────────────────────────
comps.append(place("Brew:Conn_GPIO_FREE","J12","GPIO15", 274.32, 34.29,
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                   fp="Resistor_THT:R_Axial_DIN0207_L6.3mm_D2.5mm_P7.62mm_Horizontal",
                   pins_l=R_L, pins_r=R_R))
R8x = cx(81.28); R8y = cy(83.82, 1)
# Left pin (76.2, 83.82) reached via BUZZER_CTRL route from U1 (see U1 loop)
# Right pin (86.36, 83.82) coincides with Q1(B) — no wire needed

# ── J15-J20  Combined BTN+LED panel connectors (3-pin, one per power level) ──
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comps.append(place("Brew:R","R9","10k", 256.54, 256.54,
                   fp="Resistor_THT:R_Axial_DIN0207_L6.3mm_D2.5mm_P7.62mm_Horizontal",
                   pins_l=R_L, pins_r=R_R))
lbl_l("ADC_BTN", *lpin(R9x,R9y,0,1,bw=5))
pwr_r("+3V3",    *rpin(R9x,R9y,0,1,bw=5), stub=P)

# ── R10-R14  Button ladder (BTN1-5 signal → ADC_BTN) ─────────────────────────
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    comps.append(place("Brew:R", ref, val, 256.54, ry_val,
                       fp="Resistor_THT:R_Axial_DIN0207_L6.3mm_D2.5mm_P7.62mm_Horizontal",
                       pins_l=R_L, pins_r=R_R))
    lbl_l("ADC_BTN", *lpin(rbx,rby,0,1,bw=5))
    lbl_r(btn,       *rpin(rbx,rby,0,1,bw=5))

# ── SW2-SW7  Off-board panel buttons (not on PCB) ────────────────────────────
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    bx = cx(410.21); by = cy(by_val, 1)
    comps.append(place("Brew:SW_Push", ref, desc, 410.21, by_val,
                       fp="", pins_l=SW_PUSH_L, pins_r=SW_PUSH_R, on_board=False))
    lbl_l(btn,   *lpin(bx, by, 0, 1, bw=10))  # A → BTN_n / ADC_BTN net
    pwr_r("GND", *rpin(bx, by, 0, 1, bw=10))  # B → GND

# ── LD9  Off-board power switch integrated LED (not on PCB) ──────────────────
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    (date "2026-05-25")
    (rev "1.0")
    (comment 1 "Full net-label wiring — 0 ERC violations. Generated by wire_schematic.py")
    (comment 2 "IO0=BUZZER  IO1=ADC_BTN  IO2=CS_BME  IO3=GPIO3_ADC  IO4=CS_MAX  IO5=SPI_CLK  IO6=SPI_MISO  IO7=SPI_MOSI  IO10=GPIO10  IO11=OneWire  IO15=GPIO15  IO18-20=IDS2  IO21=RELAY  IO22/23=I2C")
    (comment 3 "Power: IDS2_5V or PEXT_5V → J4 PSource (middle pin=out) → SW1 → +5V rail")
  )
  (lib_symbols
{lib_syms}
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
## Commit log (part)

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2023-04-01 Initial commit of brewingstation V1
